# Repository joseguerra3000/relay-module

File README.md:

# relay-module
Módulo de 4 Relays para uso con Arduino, PIC, Raspberry, etc...

El proyecto está hecho en KiCad y como es singel-side puede ser revelado utilizando la tecnica de la plancha o alguna otra similar.

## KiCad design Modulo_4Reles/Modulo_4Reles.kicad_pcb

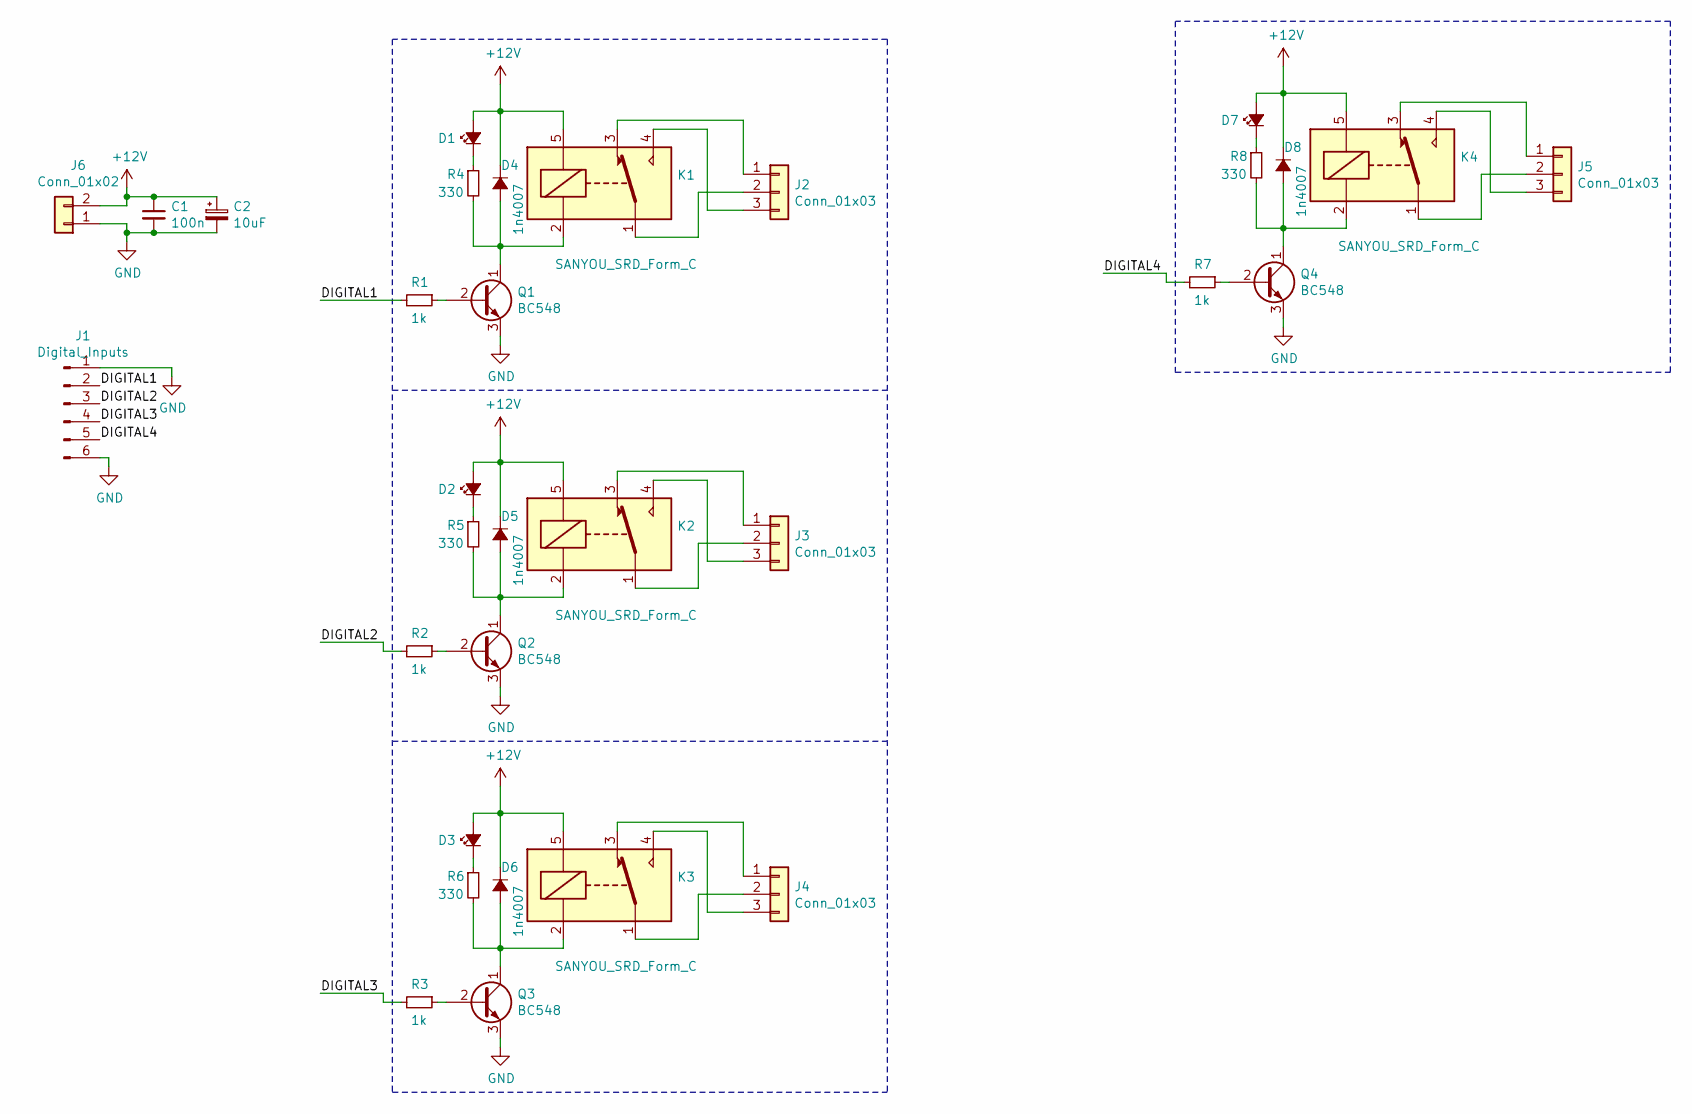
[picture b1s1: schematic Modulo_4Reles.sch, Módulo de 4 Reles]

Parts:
C1: 100n; C_Disc_D5.0mm_W2.5mm_P5.00mm
C2: 10uF; CP_Radial_D8.0mm_P2.50mm
D1, D2, D3, D7: LED_Small_ALT; LED_D5.0mm
D4, D5, D6, D8: 1n4007; D_A-405_P2.54mm_Vertical_AnodeUp
J1: Digital_Inputs; Molex_KK-254_AE-6410-06A_1x06_P2.54mm_Vertical
J2, J3, J4, J5: Conn_01x03; TerminalBlock_bornier-3_P5.08mm
J6: Conn_01x02; TerminalBlock_bornier-2_P5.08mm
K1, K2, K3, K4: SANYOU_SRD_Form_C; Relay_SPDT_SANYOU_SRD_Series_Form_C
Q1, Q2, Q3, Q4: BC548; TO-92S_Wide
R1, R2, R3, R7: 1k; R_Axial_DIN0207_L6.3mm_D2.5mm_P10.16mm_Horizontal
R4, R5, R6, R8: 330; R_Axial_DIN0207_L6.3mm_D2.5mm_P10.16mm_Horizontal

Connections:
+12V: C1.1, C2.1, D1.2 (A), D2.2 (A), D3.2 (A), D4.1 (K), D5.1 (K), D6.1 (K), D7.2 (A), D8.1 (K), J6.2, K1.5, K2.5, K3.5, K4.5
/DIGITAL1: J1.2, R1.2
/DIGITAL2: J1.3, R2.2
/DIGITAL3: J1.4, R3.2
/DIGITAL4: J1.5, R7.2
GND: C1.2, C2.2, J1.1, J1.6, J6.1, Q1.3 (E), Q2.3 (E), Q3.3 (E), Q4.3 (E)
unnamed: D1.1 (K), R4.1
unnamed: D2.1 (K), R5.1
unnamed: D3.1 (K), R6.1
unnamed: D4.2 (A), K1.2, Q1.1 (C), R4.2
unnamed: D5.2 (A), K2.2, Q2.1 (C), R5.2
unnamed: D6.2 (A), K3.2, Q3.1 (C), R6.2
unnamed: D7.1 (K), R8.1
unnamed: D8.2 (A), K4.2, Q4.1 (C), R8.2
unnamed: J2.1, K1.3
unnamed: J2.2, K1.1
unnamed: J2.3, K1.4
unnamed: J3.1, K2.3
unnamed: J3.2, K2.1
unnamed: J3.3, K2.4
unnamed: J4.1, K3.3
unnamed: J4.2, K3.1
unnamed: J4.3, K3.4
unnamed: J5.1, K4.3
unnamed: J5.2, K4.1
unnamed: J5.3, K4.4
unnamed: Q1.2 (B), R1.1
unnamed: Q2.2 (B), R2.1
unnamed: Q3.2 (B), R3.1
unnamed: Q4.2 (B), R7.1

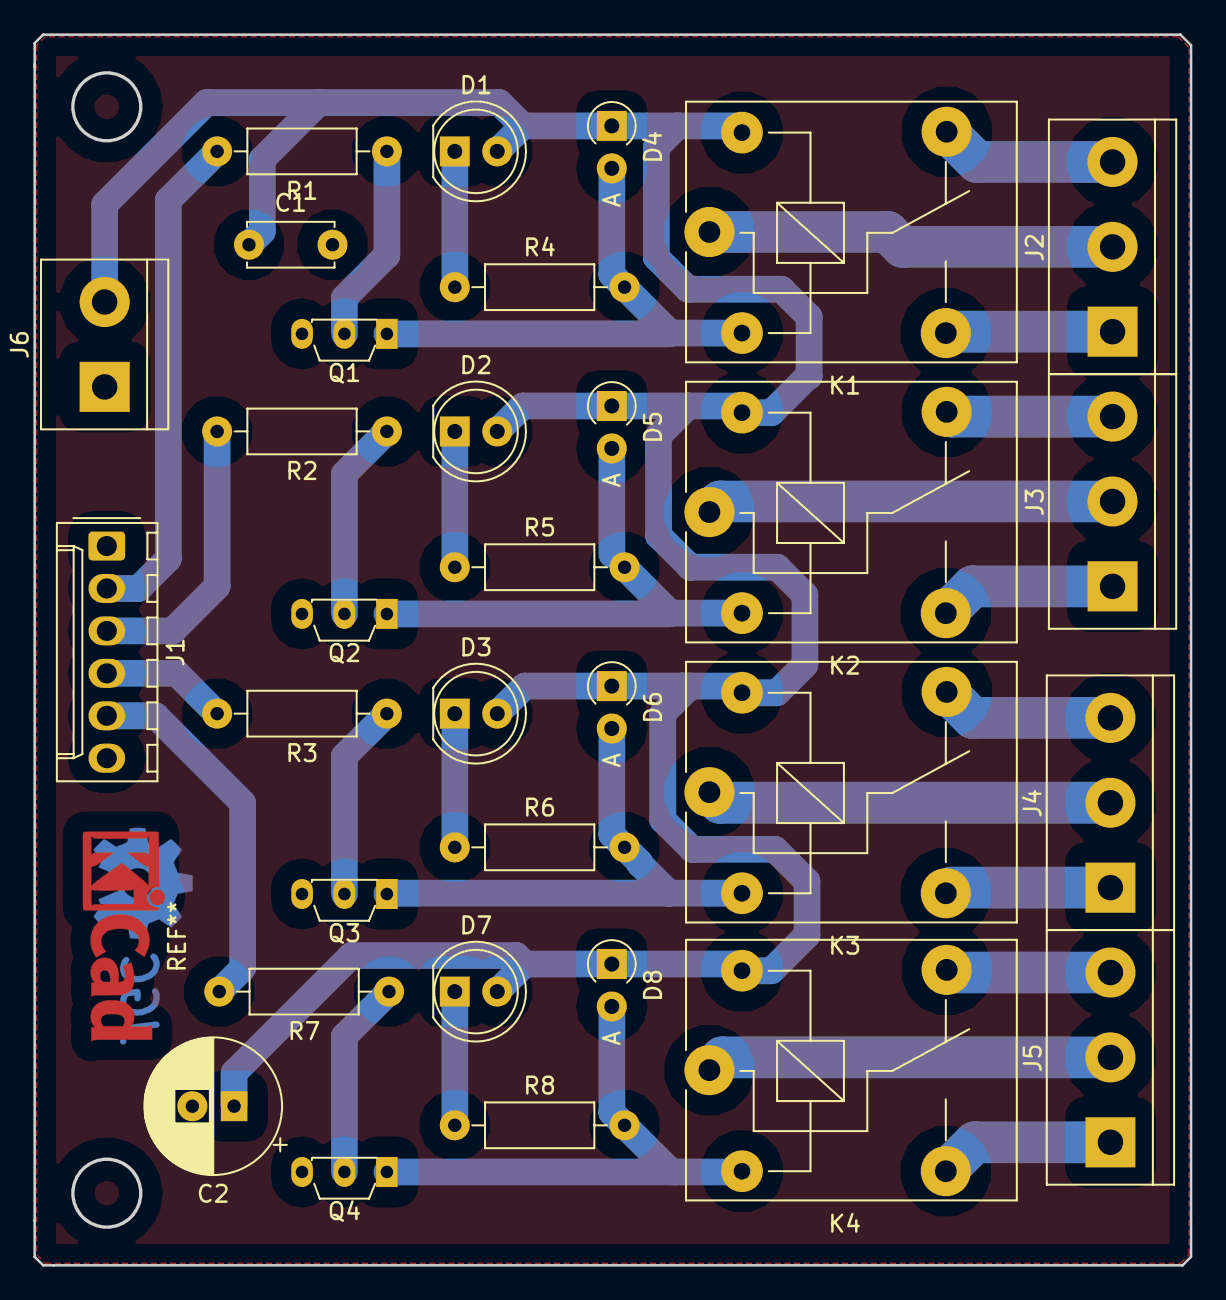
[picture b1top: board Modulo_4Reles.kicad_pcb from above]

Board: 2 copper layers, 69.2 x 73.6 mm, 32 parts (0 on the bottom side), 30 nets.

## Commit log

2019-11-14 Initial Release
